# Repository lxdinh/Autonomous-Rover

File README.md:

# Autonomous Navigation Rover

**🏆 1st Place — UCSD ECE Design Competition (Nov–Dec 2025)** · fastest pathfinding of 13 teams

> Vision-guided autonomous ground rover on a custom ESP32-S3 PCB. An ArduCAM
> OV2640 camera runs on-board RGB565 obstacle detection, an MPU6050 IMU damps the
> heading, and an L298N H-bridge drives the wheels — coordinated by a lightweight
> **FORWARD → STOP → AVOID** state machine. Everything runs on the
> microcontroller.

## Highlights

- **Custom 2-layer, 4×4 in PCB** (KiCad) integrating the ESP32-S3, OV2640,
  MPU6050, and L298N with a shared logic/motor power tree — schematic and
  Gerbers in [`hardware/`](hardware/).
- **From-scratch bare-metal drivers**, no vendor HAL: custom I²C (MPU6050),
  SPI-FIFO (ArduCAM), and LEDC-PWM (L298N) classes — 600+ lines of C++.
- **On-board vision:** per-frame red-blob detection over the middle image band,
  feeding a deterministic navigation state machine.

## Architecture

```mermaid
flowchart LR
  subgraph Sensing
    CAM[OV2640 camera<br/>SPI FIFO] --> DET[Red-blob detector<br/>RGB565, middle band]
    IMU[MPU6050<br/>I2C] --> YAW[Yaw-rate filter]
  end
  DET --> SM[Nav state machine<br/>FORWARD / STOP / AVOID]
  YAW --> MIX[Tank-drive mixer]
  SM --> MIX
  MIX --> MOT[L298N H-bridge<br/>LEDC PWM] --> W[Wheels]
```

### Navigation state machine

```mermaid
stateDiagram-v2
  [*] --> FORWARD
  FORWARD --> STOP: red band >= 20%
  STOP --> AVOID: held 200 ms and still blocked
  STOP --> FORWARD: obstacle cleared
  AVOID --> FORWARD: blob out of view
```

## Repository layout

```text
Autonomous-Rover/
├── src/
│   ├── main.cpp            # nav state machine + obstacle detection + cruise mixer
│   ├── Camera_SPI.h        # ArduCAM OV2640 over SPI FIFO (DMA buffer, BMP/RGB565)
│   ├── Sensor_I2C.h        # MPU6050 IMU (accel/gyro), bare-metal I2C
│   └── MotorDriver_PWM.h   # L298N via ESP32 LEDC PWM (Arduino core 2.x/3.x aware)
├── include/memorysaver.h   # ArduCAM camera-model selector (OV2640 Mini 2MP)
├── hardware/               # KiCad project, schematic (SVG), Gerbers
├── platformio.ini
└── README.md
```

## Hardware

| Subsystem | Part | Interface |
| --- | --- | --- |
| MCU | ESP32-S3 (DevKitC-1 class) | — |
| Camera | ArduCAM OV2640 Mini 2MP | SPI FIFO + I²C control |
| IMU | MPU6050 (accel + gyro) | I²C @ `0x68` |
| Motor driver | L298N dual H-bridge | 6 GPIO (2 PWM enables + 4 direction) |
| Power | 9 V motor pack + 3.3 V logic | common ground |

### Pin map (ESP32-S3)

| Function | GPIO | | Function | GPIO |
| --- | --- | --- | --- | --- |
| L298N ENA — left PWM | 40 | | I²C SDA | 15 |
| L298N ENB — right PWM | 39 | | I²C SCL | 17 |
| L298N IN1 / IN2 — left dir | 44 / 43 | | SPI SCK | 12 |
| L298N IN3 / IN4 — right dir | 42 / 41 | | SPI MISO | 13 |
| Camera CS | 10 | | SPI MOSI | 11 |

### Schematic

## How obstacle detection works

Each captured frame is RGB565 (one 16-bit value per pixel). The detector scans
the **middle horizontal third** of the frame — where a head-on obstacle sits —
and flags a pixel as "red" when:

| Channel | Bits | Rule |
| --- | --- | --- |
| Red | 5 (0–31) | ≥ 22 |
| Green | 6 (0–63) | ≤ 14 |
| Blue | 5 (0–31) | ≤ 14 |

If **≥ 20 %** of the band's pixels pass, the frame is treated as blocked and the
state machine reacts. All thresholds are compile-time constants in
[`src/main.cpp`](src/main.cpp) — retune `RED_MIN_5BIT`, `GREEN_MAX_6BIT`,
`BLUE_MAX_5BIT`, and `DETECTION_THRESHOLD_PERCENT` for your obstacle color and
lighting.

## Build & flash

Built with **[PlatformIO](https://platformio.org/)** (ESP32-S3 / Arduino
framework). The ArduCAM library is pulled from the PlatformIO registry
automatically; the camera model is selected via the `-DOV2640_MINI_2MP` build
flag in [`platformio.ini`](platformio.ini).

```bash
# from the repo root
pio run                        # compile
pio run -t upload              # flash (board on its native USB port)
pio device monitor -b 115200   # serial @ 115200
```

**Arduino IDE** users: install the **ArduCAM** library, provide a `memorysaver.h`
with `#define OV2640_MINI_2MP`, select an ESP32-S3 board with **USB CDC On Boot:
Enabled**, and build `src/main.cpp`.

## Design notes & tuning

- **Motor duty is capped** to `MOTOR_MAX_DUTY_PCT` (85 %) so that simultaneous
  acceleration on a sagging 9 V pack does not brown out the 3.3 V logic rail.
- **Camera resolution is read from the BMP header** on every capture, so the
  pipeline is robust to QVGA/QCIF differences across ArduCAM firmware revisions.
- **Heading hold:** the MPU6050 yaw-rate currently applies gentle equal-wheel
  damping. Promoting it to a *differential* correction (opposite sign per wheel)
  is the natural next step for tighter straight-line tracking; the mixer already
  exposes a symmetric correction term to build on.

## License

MIT — see [LICENSE](LICENSE). Firmware and hardware authored for the UCSD ECE
Design Competition.

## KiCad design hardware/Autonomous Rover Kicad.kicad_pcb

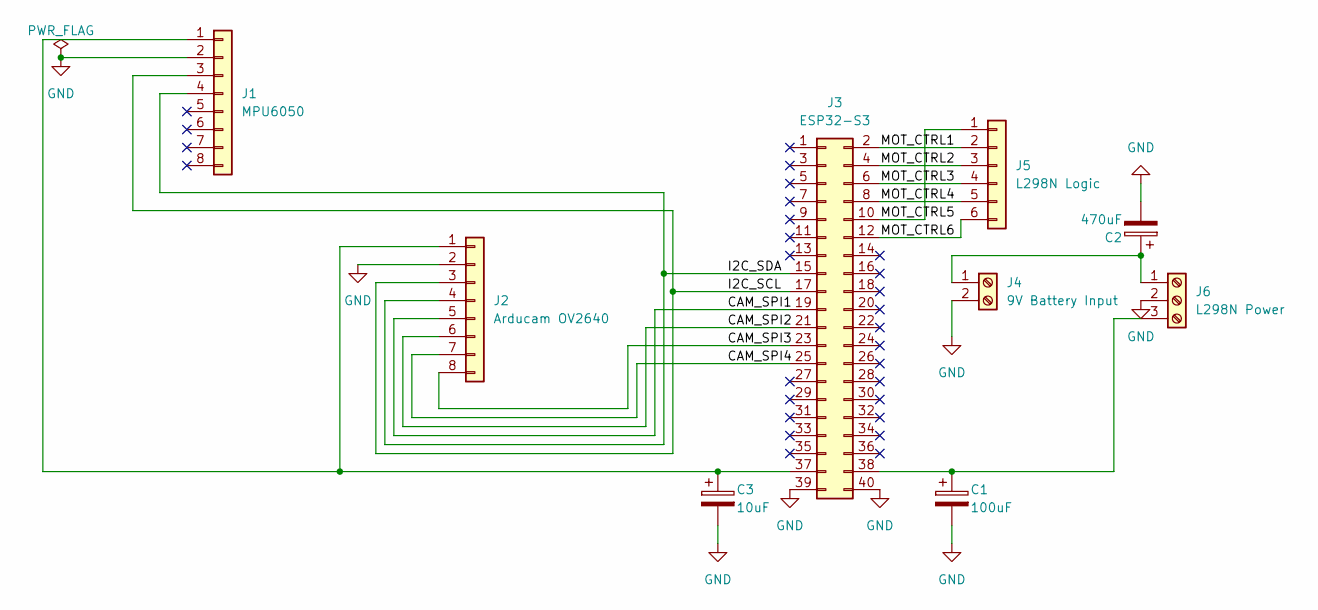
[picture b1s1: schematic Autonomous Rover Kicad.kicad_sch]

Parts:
C1: 100uF; CP_Radial_D6.3mm_P2.50mm
C2: 470uF; CP_Radial_D8.0mm_P3.50mm
C3: 10uF; CP_Radial_D5.0mm_P2.50mm
J1: MPU6050; PinHeader_1x08_P2.54mm_Vertical
J2: Arducam OV2640; PinHeader_1x08_P2.54mm_Vertical
J3: ESP32-S3; PinHeader_2x20_P2.54mm_Vertical
J4: 9V Battery Input; TerminalBlock_Phoenix_PT-1,5-2-3.5-H_1x02_P3.50mm_Horizontal
J5: L298N Logic; PinHeader_1x06_P2.54mm_Vertical
J6: L298N Power; TerminalBlock_Phoenix_PT-1,5-3-3.5-H_1x03_P3.50mm_Horizontal

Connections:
/CAM_SPI1: J2.5, J3.19
/CAM_SPI2: J2.6, J3.21
/CAM_SPI3: J2.8, J3.23
/CAM_SPI4: J2.7, J3.25
/I2C_SCL: J1.3, J2.3, J3.17
/I2C_SDA: J1.4, J2.4, J3.15
/MOT_CTRL1: J3.2, J5.2
/MOT_CTRL2: J3.4, J5.3
/MOT_CTRL3: J3.6, J5.4
/MOT_CTRL4: J3.8, J5.5
/MOT_CTRL5: J3.10, J5.1
/MOT_CTRL6: J3.12, J5.6
GND: C1.2, C2.2, C3.2, J1.2, J2.2, J3.39, J3.40, J4.2, J6.2
unnamed: C3.1, J1.1, J2.1, J3.37
unnamed: C1.1, J3.38, J6.3
unnamed: C2.1, J4.1, J6.1

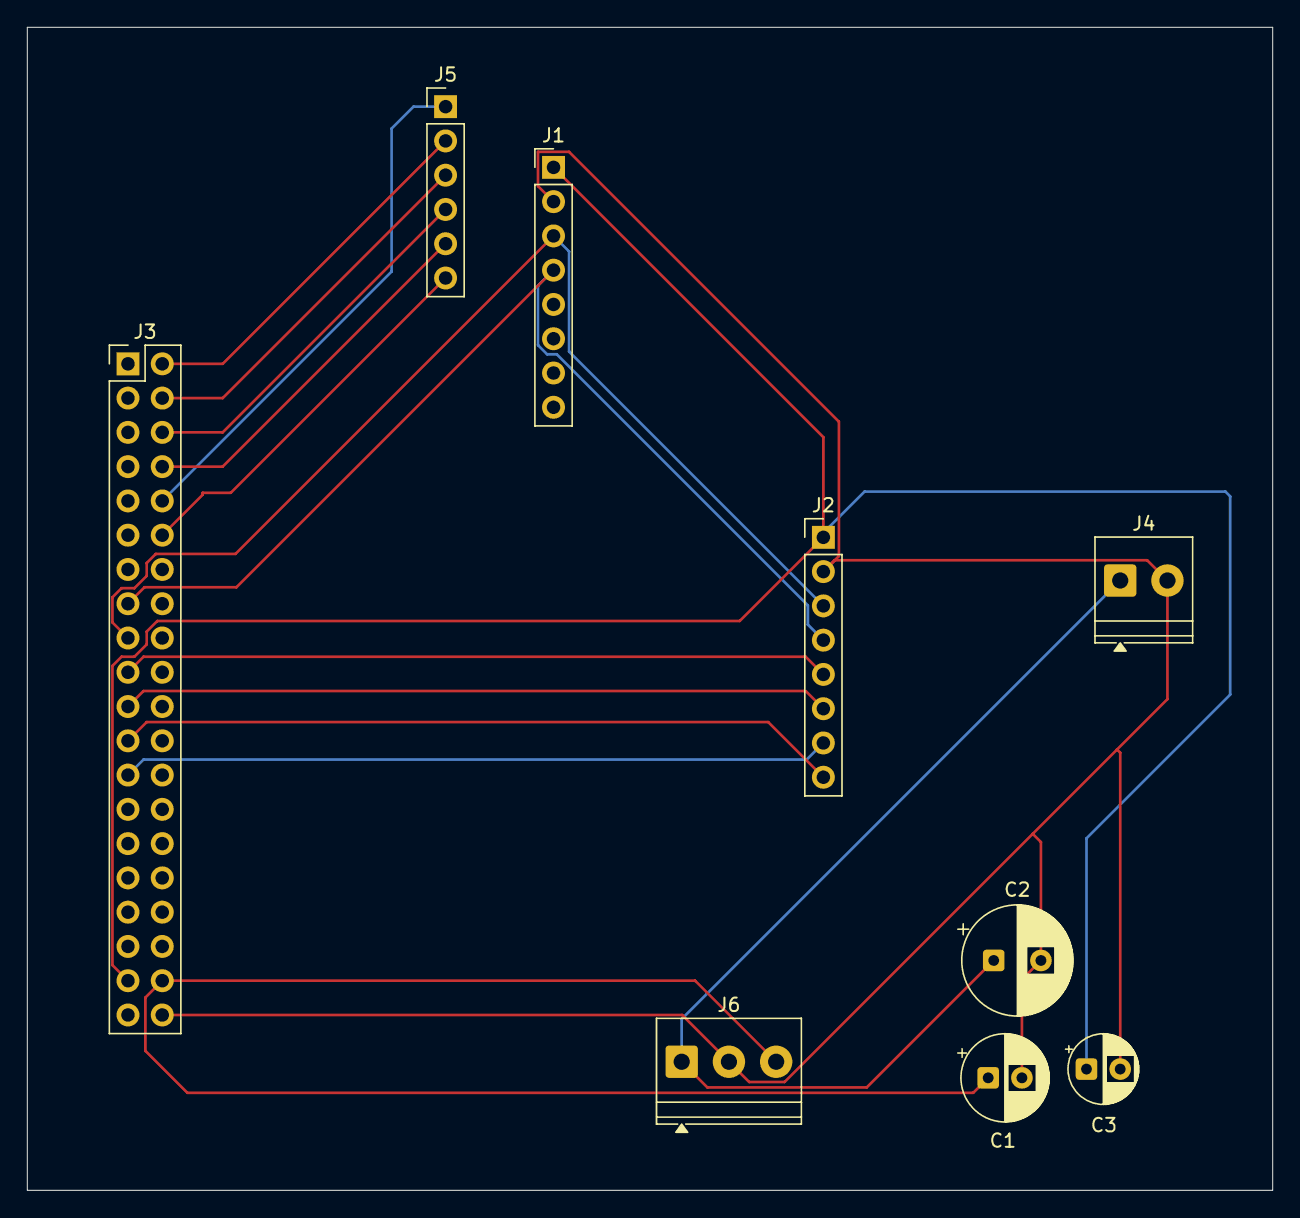
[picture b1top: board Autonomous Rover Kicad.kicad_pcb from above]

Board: 2 copper layers, 92.3 x 86.2 mm, 9 parts (0 on the bottom side), 16 nets.

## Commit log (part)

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2026-03-29 Initial release
2026-03-29 Embed schematic image into README
